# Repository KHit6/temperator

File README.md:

# temperator 
## Smart connected device to measure 8 temperatures and 2 AC currents

temperator is a robust and easy-to-use measurement system for taking 8 temperatures and 2 AC currents. Its design is simple yet professional. No special knowledge is required for operation. In addition to the hardware, a configuration for operation with [ESPHome](https://esphome.io/) is provided in a [separate repository](https://github.com/KHit6/temperator-esphome/). This makes integration with [Home Assistant](https://www.home-assistant.io/) or other home automation systems very easy. Besides legacy Home Assistant connectivity, MQTT as interface protocol is also supported.

Each measurement channel is handled individually. This avoids the very common incompatibilities and difficulties in use when connecting multiple OneWire sensors together. E.g. it takes less than one minute to exchange a sensor - no more struggling with DS18B20's unique ids. Sensors with a cable length of more than 10 meters can be used without any problems. To adjust to the CT's type you can set a separate gain for each current transformer.

Particular emphasis was placed on ease of use and robust operation and favorable overall costs. A 2-layer board was sufficient for the PCB.

Further design goals of this project included:

 * Provides 8 individual channels to acquire temperatures with very common DS18B20 sensors
 * Provides 2 channels to acquire AC current values with common current transformers
 * Provides an on-board display for quick viewing of temperatures and currents
 * Use of an available ESP32 development board with a least second source available 
 * Use of terminal clamps to connect sensors without any tools
 * The terminal clamps allows to use stranded wires
 * Protect all inputs against ESD damages
 * No handling of mains voltage necessary
 * The board's design fits in an of the shelf case
 * Use common and available components – although is has to be a THT design to get it produced in very small quantities or by DIY hobbyists
 * Offers ESPHOME-generated software for connecting either to Home Assistant or via MQTT to other home automation systems

As micro-controller an [Arduino Nano ESP32](https://docs.arduino.cc/hardware/nano-esp32/) is used. This, or compatible models, offer sufficient resources to program even more complex control systems. It also allows the use of MicroPython, alternatively. Maybe, but that was no design goal, other Arduino Nanos can be used as well.

Here are some impressions of a fully assembled temperator:

## Some Hints
 * The CT's bandpass filter stage is calculated according this [tutorial](https://www.electronics-tutorials.ws/de/filtern/aktiver-bandpassfilter.html). AC voltage input and hence output of the transformer is assumed to be 1 Vpp. The intended gain is 3.83 and the cutoff frequencies are about 90 Hz and 10 Hz
 * The display must have its pins in the order GND, VCC, SCL, SDA. Caution, you can buy displays with the same name but different GND VCC orders
 * The board offers the flexibility to use two different display sizes. Two diagonally opposite screw fixings are provided for each size. Unfortunately there is no "standard" with this kind of display modules, so sometimes the screw holes may not match.
 * With an Arduino board you must not assemble the "Boot" pin header
 * The current transformer inputs can alternatively be used for other analogue AC signals than signals from current transformers
 * Each analogue input provide a low current 3.3V voltage source to supply external circuits
 * The bill of material (BOM) is enhanced with all mechanical parts like screws, stands and the case

## Todos
 * Currently temperator (Version V1.1) source all voltages to the temperature sensors directly from the ESP32 module's voltage regulator. There must be  protection circuit built in to protect the regulator.
 * Very rare DS18B20 cease to send data. It would be helpful if the supply voltage of the sensors can be remotely switched off and on again to restart the sensors.

As EDA system KiCAD 9.06 was used (Great EDA tool).

temperator is subject to the "CERN OHL V2 Weakly License".

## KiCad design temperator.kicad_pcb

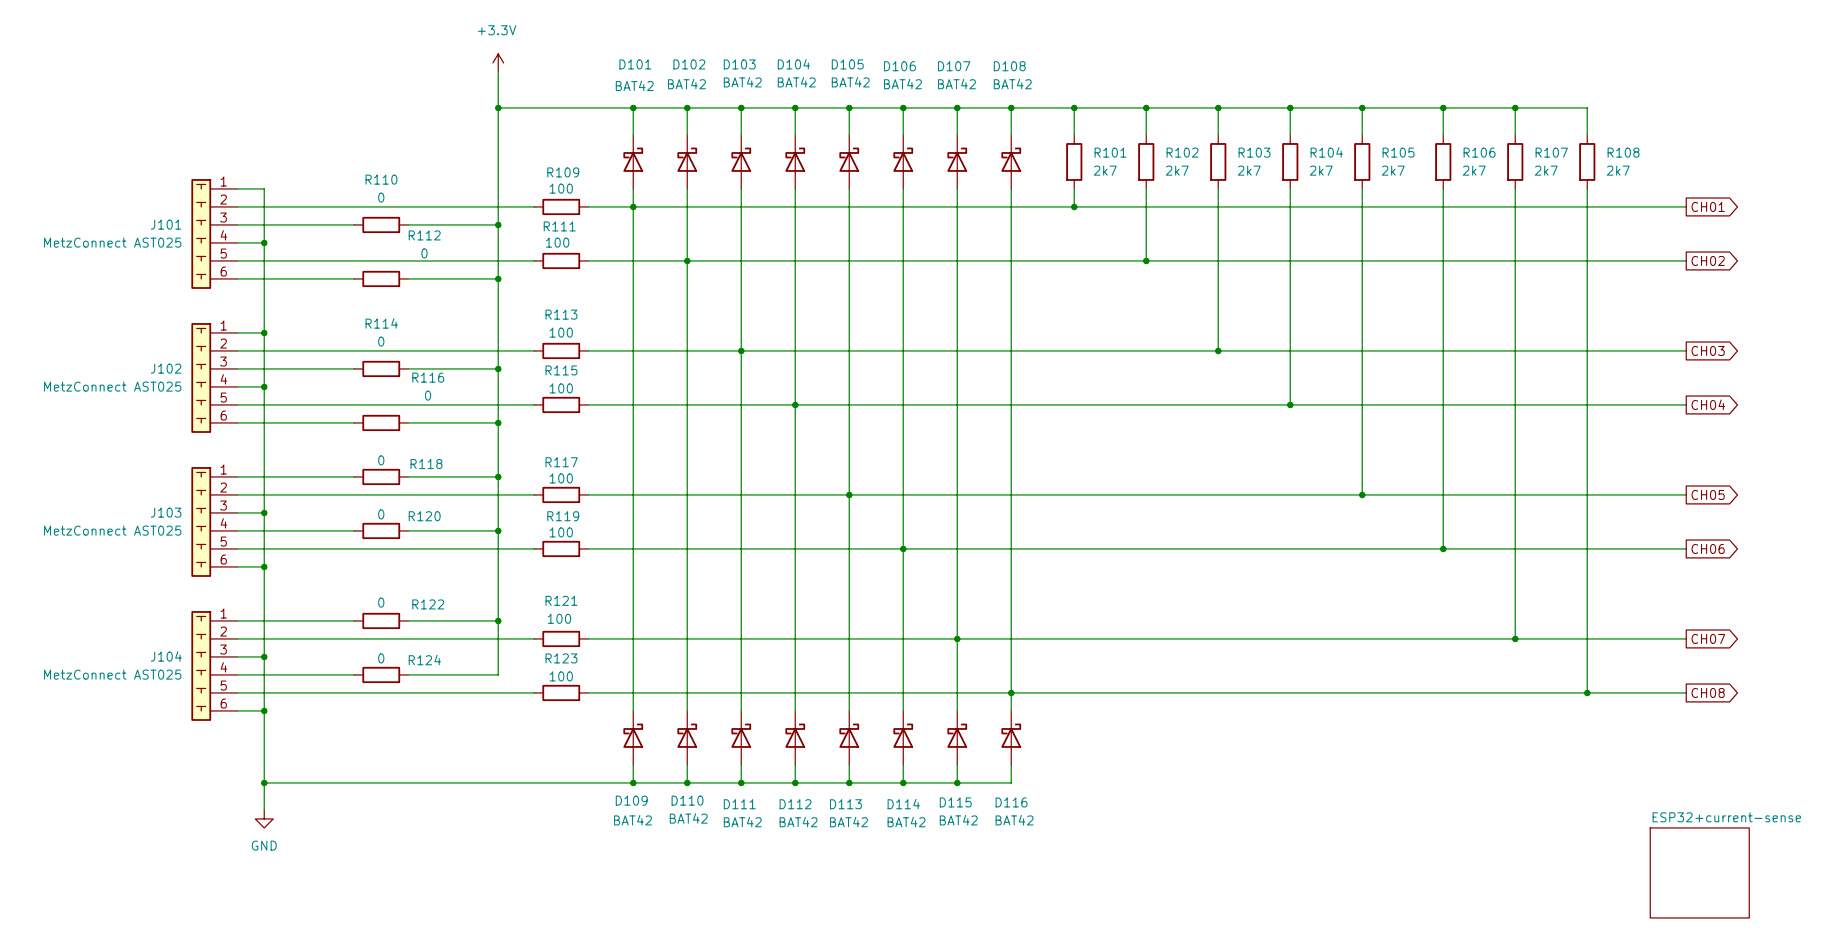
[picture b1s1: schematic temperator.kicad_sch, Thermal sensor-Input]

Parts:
D101, D102, D103, D104, D105, D106, D107, D108, D109, D110, D111, D112, D113, D114, D115, D116: BAT42; D_DO-35_SOD27_P7.62mm_Horizontal
J101, J102, J103, J104: MetzConnect AST025; TerminalBlock_MetzConnect_AST025_1x06_P5.00mm_Horizontal
R101, R102, R103, R104, R105, R106, R107, R108: 2k7; R_Axial_DIN0204_L3.6mm_D1.6mm_P7.62mm_Horizontal
R109, R111, R113, R115, R117, R119, R121, R123: 100; R_Axial_DIN0204_L3.6mm_D1.6mm_P7.62mm_Horizontal
R110, R112, R114, R116, R118, R120, R122, R124: 0; R_Axial_DIN0204_L3.6mm_D1.6mm_P7.62mm_Horizontal

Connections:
+3.3V: D101.1 (K), D102.1 (K), D103.1 (K), D104.1 (K), D105.1 (K), D106.1 (K), D107.1 (K), D108.1 (K), R101.1, R102.1, R103.1, R104.1, R105.1, R106.1, R107.1, R108.1, R110.2, R112.2, R114.2, R116.2, R118.2, R120.2, R122.2, R124.2; also elsewhere on the board
CH01: D101.2 (A), D109.1 (K), R101.2, R109.2; also elsewhere on the board
CH02: D102.2 (A), D110.1 (K), R102.2, R111.2; also elsewhere on the board
CH03: D103.2 (A), D111.1 (K), R103.2, R113.2; also elsewhere on the board
CH04: D104.2 (A), D112.1 (K), R104.2, R115.2; also elsewhere on the board
CH05: D105.2 (A), D113.1 (K), R105.2, R117.2; also elsewhere on the board
CH06: D106.2 (A), D114.1 (K), R106.2, R119.2; also elsewhere on the board
CH07: D107.2 (A), D115.1 (K), R107.2, R121.2; also elsewhere on the board
CH08: D108.2 (A), D116.1 (K), R108.2, R123.2; also elsewhere on the board
GND: D109.2 (A), D110.2 (A), D111.2 (A), D112.2 (A), D113.2 (A), D114.2 (A), D115.2 (A), D116.2 (A), J101.1, J101.4, J102.1, J102.4, J103.3, J103.6, J104.3, J104.6; also elsewhere on the board
unnamed: J101.2, R109.1
unnamed: J101.3, R110.1
unnamed: J101.5, R111.1
unnamed: J101.6, R112.1
unnamed: J102.2, R113.1
unnamed: J102.3, R114.1
unnamed: J102.5, R115.1
unnamed: J102.6, R116.1
unnamed: J103.1, R118.1
unnamed: J103.2, R117.1
unnamed: J103.4, R120.1
unnamed: J103.5, R119.1
unnamed: J104.1, R122.1
unnamed: J104.2, R121.1
unnamed: J104.4, R124.1
unnamed: J104.5, R123.1

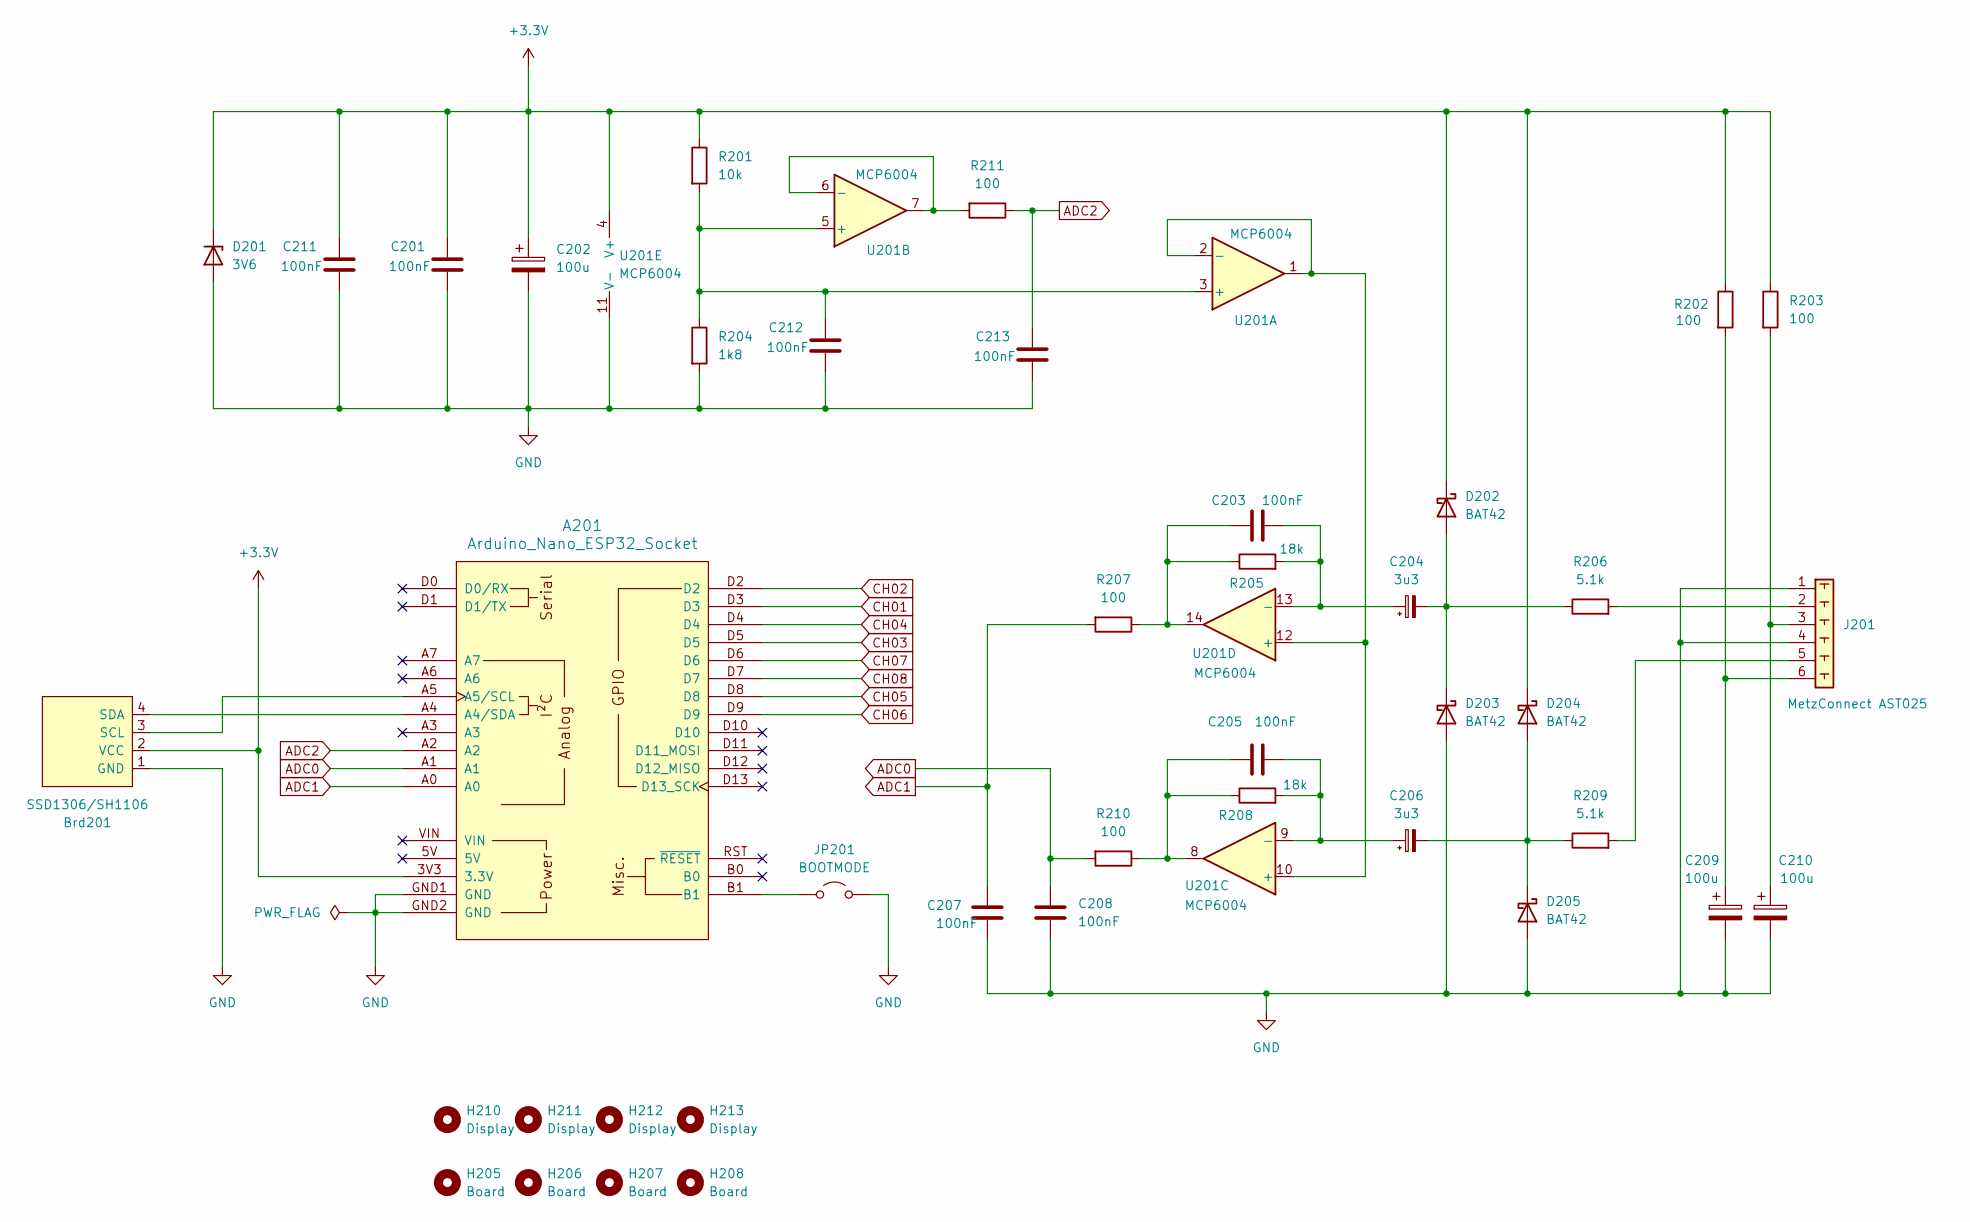
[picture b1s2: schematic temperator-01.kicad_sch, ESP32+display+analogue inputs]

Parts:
A201: Arduino_Nano_ESP32_Socket
Brd201: SSD1306/SH1106; PinHeader_1x04_P2.54mm_Vertical
C201, C207, C208, C211, C212, C213: 100nF; C_Rect_L4.6mm_W3.8mm_P2.50mm_MKS02_FKP02
C202, C209, C210: 100u; CP_Radial_D6.3mm_P2.50mm
C203, C205: 100nF; C_Rect_L4.6mm_W3.0mm_P2.50mm_MKS02_FKP02
C204, C206: 3u3; CP_Radial_Tantal_D4.5mm_P2.50mm
D201: 3V6; D_DO-15_P10.16mm_Horizontal
D202, D203, D204, D205: BAT42; D_DO-35_SOD27_P7.62mm_Horizontal
H205, H206, H207, H208: Board; MountingHole_3.2mm_M3_DIN965_Pad_TopBottom
H210, H211, H212, H213: Display; MountingHole_2.2mm_M2_DIN965_Pad_TopBottom
J201: MetzConnect AST025; TerminalBlock_MetzConnect_AST025_1x06_P5.00mm_Horizontal
JP201: BOOTMODE; PinHeader_1x02_P2.54mm_Vertical
R201: 10k; R_Axial_DIN0204_L3.6mm_D1.6mm_P7.62mm_Horizontal
R202, R203, R207, R210, R211: 100; R_Axial_DIN0204_L3.6mm_D1.6mm_P7.62mm_Horizontal
R204: 1k8; R_Axial_DIN0204_L3.6mm_D1.6mm_P7.62mm_Horizontal
R205, R208: 18k; R_Axial_DIN0204_L3.6mm_D1.6mm_P7.62mm_Horizontal
R206, R209: 5.1k; R_Axial_DIN0204_L3.6mm_D1.6mm_P7.62mm_Horizontal
U201: MCP6004; DIP-14_W7.62mm

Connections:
+3.3V: A201.3V3 (3.3V), Brd201.2 (VCC), C201.1, C202.1, C211.1, D201.1 (K), D202.1 (K), D204.1 (K), R201.1, R202.1, R203.1, U201.4 (V+); also elsewhere on the board
ADC0: A201.A1, C208.1, R210.2
ADC1: A201.A0, C207.1, R207.2
ADC2: A201.A2, C213.1, R211.1
CH01: A201.D3; also elsewhere on the board
CH02: A201.D2; also elsewhere on the board
CH03: A201.D5; also elsewhere on the board
CH04: A201.D4; also elsewhere on the board
CH05: A201.D8; also elsewhere on the board
CH06: A201.D9; also elsewhere on the board
CH07: A201.D6; also elsewhere on the board
CH08: A201.D7; also elsewhere on the board
GND: A201.GND1 (GND), A201.GND2 (GND), Brd201.1 (GND), C201.2, C202.2, C207.2, C208.2, C209.2, C210.2, C211.2, C212.2, C213.2, D201.2 (A), D203.2 (A), D205.2 (A), J201.1, J201.4, JP201.2 (B), R204.2, U201.11 (V-); also elsewhere on the board
unnamed: A201.A4 (A4/SDA), Brd201.4 (SDA)
unnamed: A201.A5 (A5/SCL), Brd201.3 (SCL)
unnamed: C203.1, R205.1, R207.1, U201.14
unnamed: C205.1, R208.1, R210.1, U201.8
unnamed: C204.2, D202.2 (A), D203.1 (K), R206.1
unnamed: C206.2, D204.2 (A), D205.1 (K), R209.1
unnamed: J201.2, R206.2
unnamed: C210.1, J201.3, R203.2
unnamed: J201.5, R209.2
unnamed: C209.1, J201.6, R202.2
unnamed: A201.B1, JP201.1 (A)
unnamed: C212.1, R201.2, R204.1, U201.3 (+), U201.5 (+)
unnamed: U201.1, U201.2 (-), U201.10 (+), U201.12 (+)
unnamed: R211.2, U201.6 (-), U201.7
unnamed: C205.2, C206.1, R208.2, U201.9 (-)
unnamed: C203.2, C204.1, R205.2, U201.13 (-)

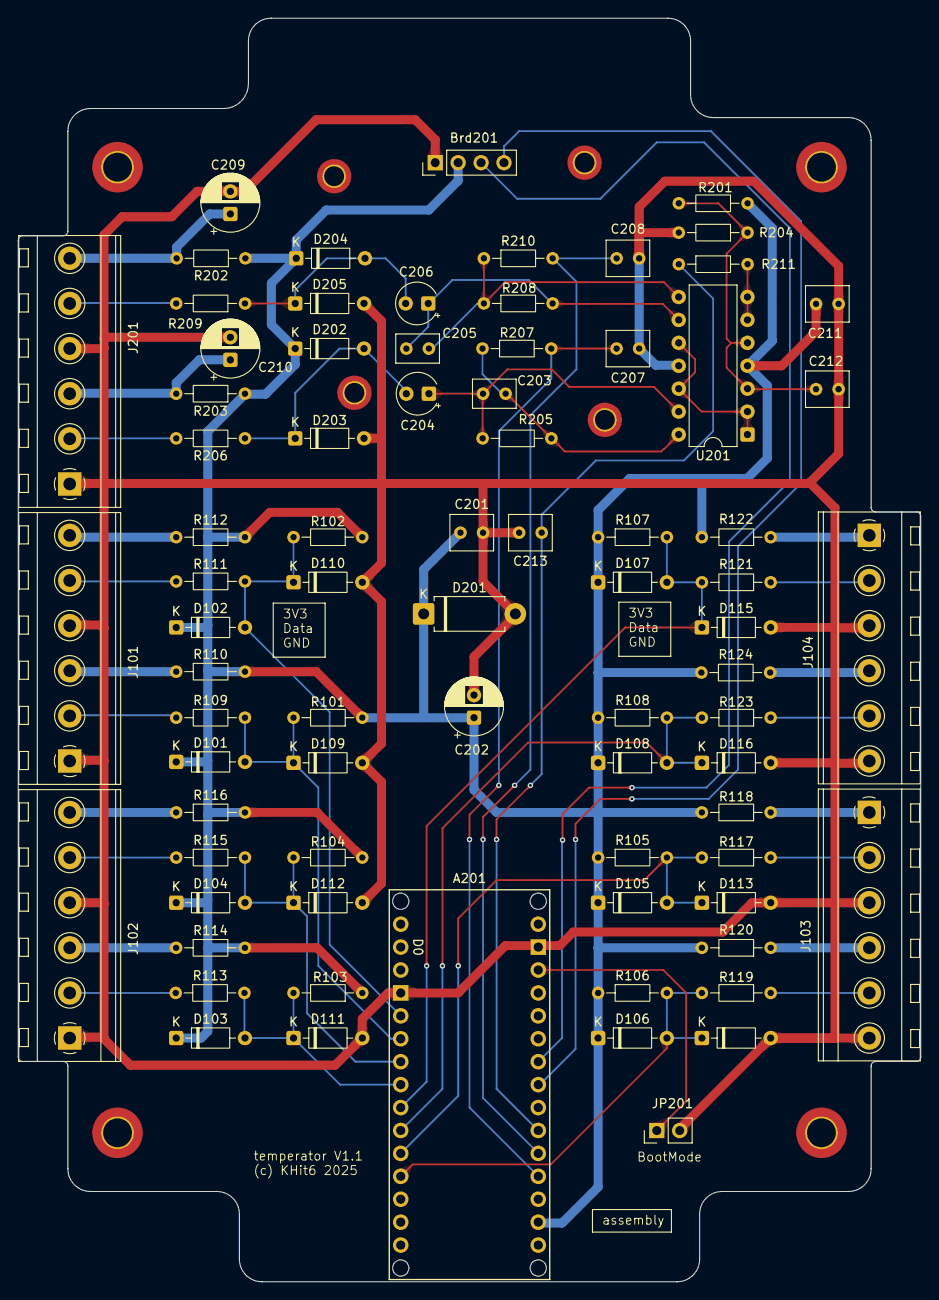
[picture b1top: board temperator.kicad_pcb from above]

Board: 2 copper layers, 100.0 x 140.0 mm, 86 parts (0 on the bottom side), 45 nets.

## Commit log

2025-12-14 fixed some typos
2025-12-15 link added to temperator-esphome
2026-01-04 added a terminal layout diagram
2026-03-21 removed BOM bug and enhanced information in BOM
2026-03-24 additional BOM corrections and enhancements
